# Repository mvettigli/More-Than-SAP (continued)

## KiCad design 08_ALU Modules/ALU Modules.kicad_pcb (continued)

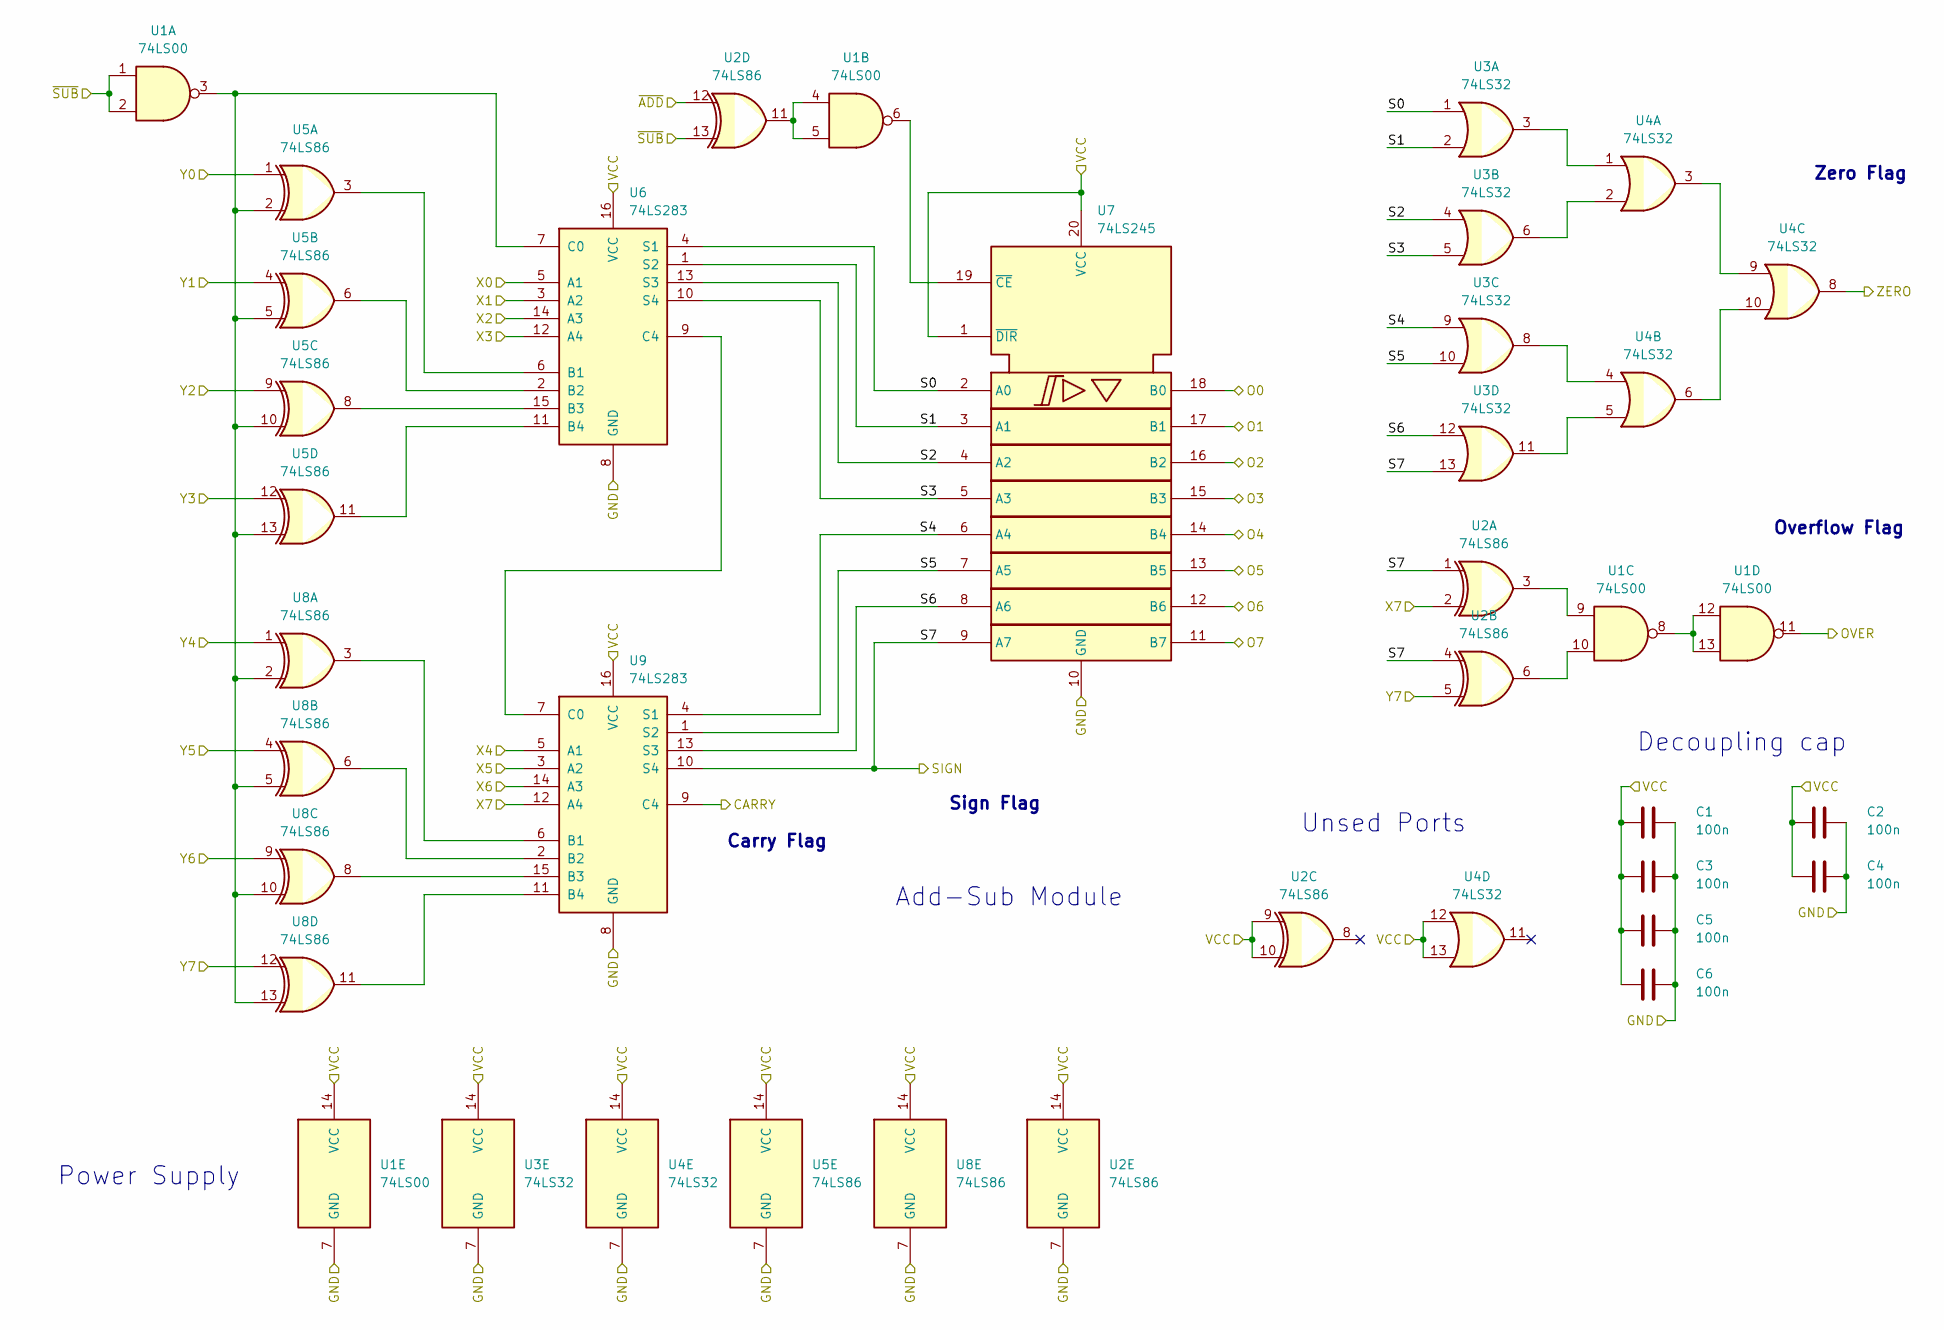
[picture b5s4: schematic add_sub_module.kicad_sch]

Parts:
C1, C2, C3, C4, C5, C6: 100n; C_Disc_D3.0mm_W1.6mm_P2.50mm
U1: 74LS00; DIP-14_W7.62mm
U2, U5, U8: 74LS86; DIP-14_W7.62mm
U3, U4: 74LS32; DIP-14_W7.62mm
U6, U9: 74LS283; DIP-16_W7.62mm
U7: 74LS245; DIP-20_W7.62mm

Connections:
/Add-Sub Module/S0: U3.1, U6.4 (S1), U7.2 (A0)
/Add-Sub Module/S1: U3.2, U6.1 (S2), U7.3 (A1)
/Add-Sub Module/S2: U3.4, U6.13 (S3), U7.4 (A2)
/Add-Sub Module/S3: U3.5, U6.10 (S4), U7.5 (A3)
/Add-Sub Module/S4: U3.9, U7.6 (A4), U9.4 (S1)
/Add-Sub Module/S5: U3.10, U7.7 (A5), U9.1 (S2)
/Add-Sub Module/S6: U3.12, U7.8 (A6), U9.13 (S3)
CARRY: U9.9 (C4); also elsewhere on the board
GND: C1.2, C2.2, C3.2, C4.2, C5.2, C6.2, U1.7 (GND), U2.7 (GND), U3.7 (GND), U4.7 (GND), U5.7 (GND), U6.8 (GND), U7.10 (GND), U8.7 (GND), U9.8 (GND); also elsewhere on the board
unnamed: U1.4, U1.5, U2.11
unnamed: U1.9, U2.3
unnamed: U1.10, U2.6
unnamed: U1.8, U1.12, U1.13
unnamed: U3.3, U4.1
unnamed: U3.6, U4.2
unnamed: U3.8, U4.4
unnamed: U3.11, U4.5
unnamed: U4.3, U4.9
unnamed: U4.6, U4.10
unnamed: U5.3, U6.6 (B1)
unnamed: U5.6, U6.2 (B2)
unnamed: U5.8, U6.15 (B3)
unnamed: U5.11, U6.11 (B4)
unnamed: U1.3, U5.2, U5.5, U5.10, U5.13, U6.7 (C0), U8.2, U8.5, U8.10, U8.13
unnamed: U6.9 (C4), U9.7 (C0)
unnamed: U1.6, U7.19 (~CE)
unnamed: U8.3, U9.6 (B1)
unnamed: U8.6, U9.2 (B2)
unnamed: U8.8, U9.15 (B3)
unnamed: U8.11, U9.11 (B4)
O0: U7.18 (B0); also elsewhere on the board
O1: U7.17 (B1); also elsewhere on the board
O2: U7.16 (B2); also elsewhere on the board
O3: U7.15 (B3); also elsewhere on the board
O4: U7.14 (B4); also elsewhere on the board
O5: U7.13 (B5); also elsewhere on the board
O6: U7.12 (B6); also elsewhere on the board
O7: U7.11 (B7); also elsewhere on the board
OVER: U1.11; also elsewhere on the board
SIGN: U2.1, U2.4, U3.13, U7.9 (A7), U9.10 (S4); also elsewhere on the board
VCC: C1.1, C2.1, C3.1, C4.1, C5.1, C6.1, U1.14 (VCC), U2.9, U2.10, U2.14 (VCC), U3.14 (VCC), U4.12, U4.13, U4.14 (VCC), U5.14 (VCC), U6.16 (VCC), U7.1 (~DIR), U7.20 (VCC), U8.14 (VCC), U9.16 (VCC); also elsewhere on the board
X0: U6.5 (A1); also elsewhere on the board
X1: U6.3 (A2); also elsewhere on the board
X2: U6.14 (A3); also elsewhere on the board
X3: U6.12 (A4); also elsewhere on the board
X4: U9.5 (A1); also elsewhere on the board
X5: U9.3 (A2); also elsewhere on the board
X6: U9.14 (A3); also elsewhere on the board
X7: U2.2, U9.12 (A4); also elsewhere on the board
Y0: U5.1; also elsewhere on the board
Y1: U5.4; also elsewhere on the board
Y2: U5.9; also elsewhere on the board
Y3: U5.12; also elsewhere on the board
Y4: U8.1; also elsewhere on the board
Y5: U8.4; also elsewhere on the board
Y6: U8.9; also elsewhere on the board
Y7: U2.5, U8.12; also elsewhere on the board
ZERO: U4.8; also elsewhere on the board
~ADD: U2.12; also elsewhere on the board
~SUB: U1.1, U1.2, U2.13; also elsewhere on the board

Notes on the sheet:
Carry Flag
Decoupling cap
Add-Sub Module
Unsed Ports
Sign Flag
Zero Flag
Power Supply
Overflow Flag

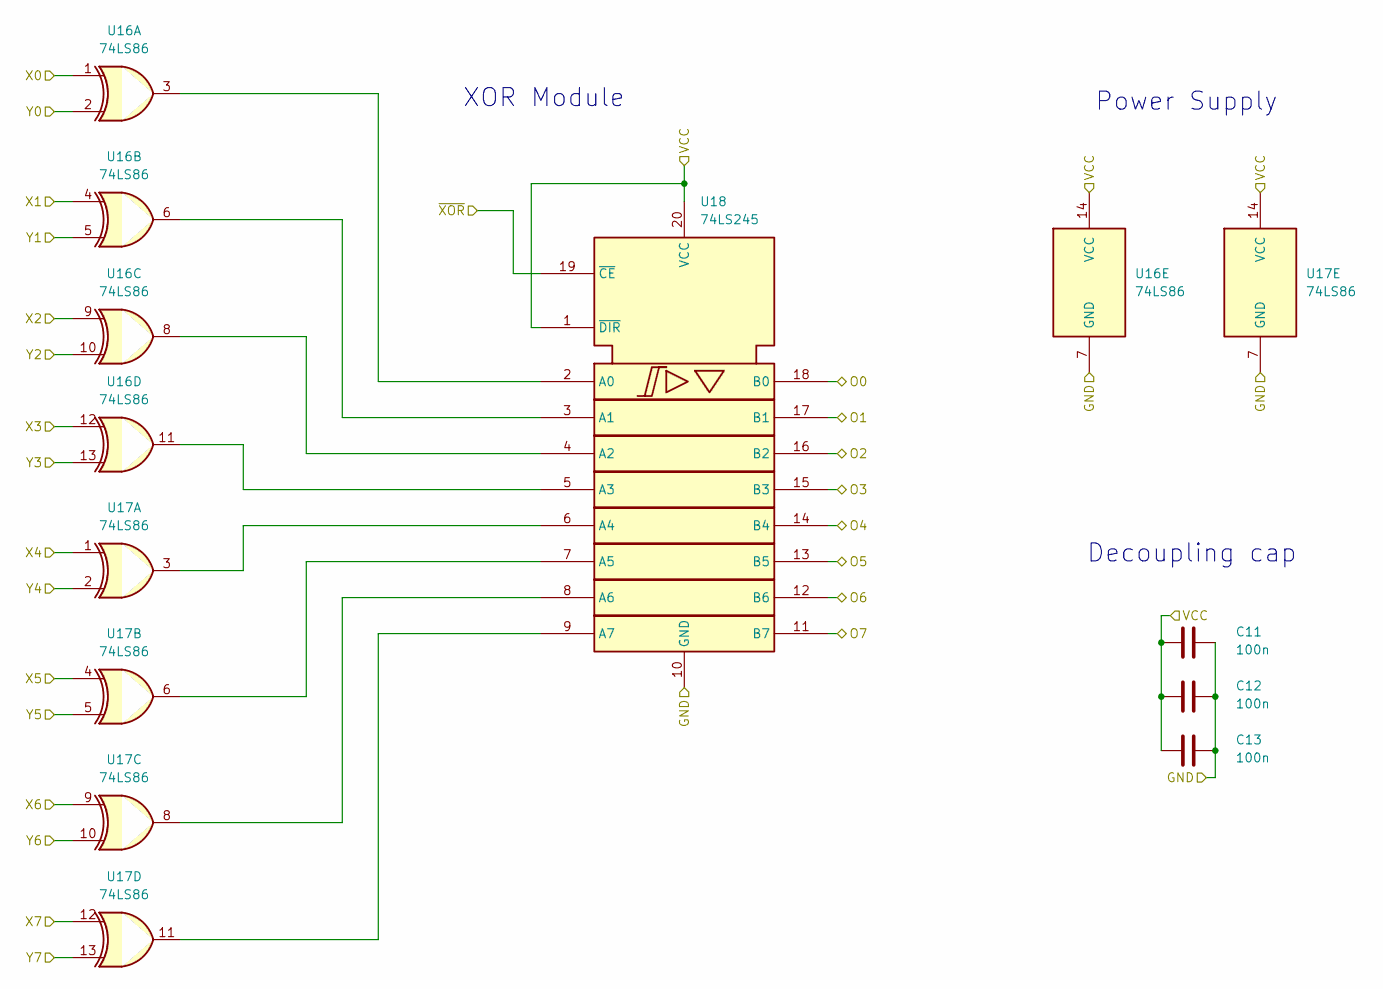
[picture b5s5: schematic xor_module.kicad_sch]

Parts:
C11, C12, C13: 100n; C_Disc_D3.0mm_W1.6mm_P2.50mm
U16, U17: 74LS86; DIP-14_W7.62mm
U18: 74LS245; DIP-20_W7.62mm

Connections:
GND: C11.2, C12.2, C13.2, U16.7 (GND), U17.7 (GND), U18.10 (GND); also elsewhere on the board
unnamed: U16.3, U18.2 (A0)
unnamed: U16.6, U18.3 (A1)
unnamed: U16.8, U18.4 (A2)
unnamed: U16.11, U18.5 (A3)
unnamed: U17.3, U18.6 (A4)
unnamed: U17.6, U18.7 (A5)
unnamed: U17.8, U18.8 (A6)
unnamed: U17.11, U18.9 (A7)
O0: U18.18 (B0); also elsewhere on the board
O1: U18.17 (B1); also elsewhere on the board
O2: U18.16 (B2); also elsewhere on the board
O3: U18.15 (B3); also elsewhere on the board
O4: U18.14 (B4); also elsewhere on the board
O5: U18.13 (B5); also elsewhere on the board
O6: U18.12 (B6); also elsewhere on the board
O7: U18.11 (B7); also elsewhere on the board
VCC: C11.1, C12.1, C13.1, U16.14 (VCC), U17.14 (VCC), U18.1 (~DIR), U18.20 (VCC); also elsewhere on the board
X0: U16.1; also elsewhere on the board
X1: U16.4; also elsewhere on the board
X2: U16.9; also elsewhere on the board
X3: U16.12; also elsewhere on the board
X4: U17.1; also elsewhere on the board
X5: U17.4; also elsewhere on the board
X6: U17.9; also elsewhere on the board
X7: U17.12; also elsewhere on the board
Y0: U16.2; also elsewhere on the board
Y1: U16.5; also elsewhere on the board
Y2: U16.10; also elsewhere on the board
Y3: U16.13; also elsewhere on the board
Y4: U17.2; also elsewhere on the board
Y5: U17.5; also elsewhere on the board
Y6: U17.10; also elsewhere on the board
Y7: U17.13; also elsewhere on the board
~XOR: U18.19 (~CE); also elsewhere on the board

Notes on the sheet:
Decoupling cap
Power Supply
XOR Module

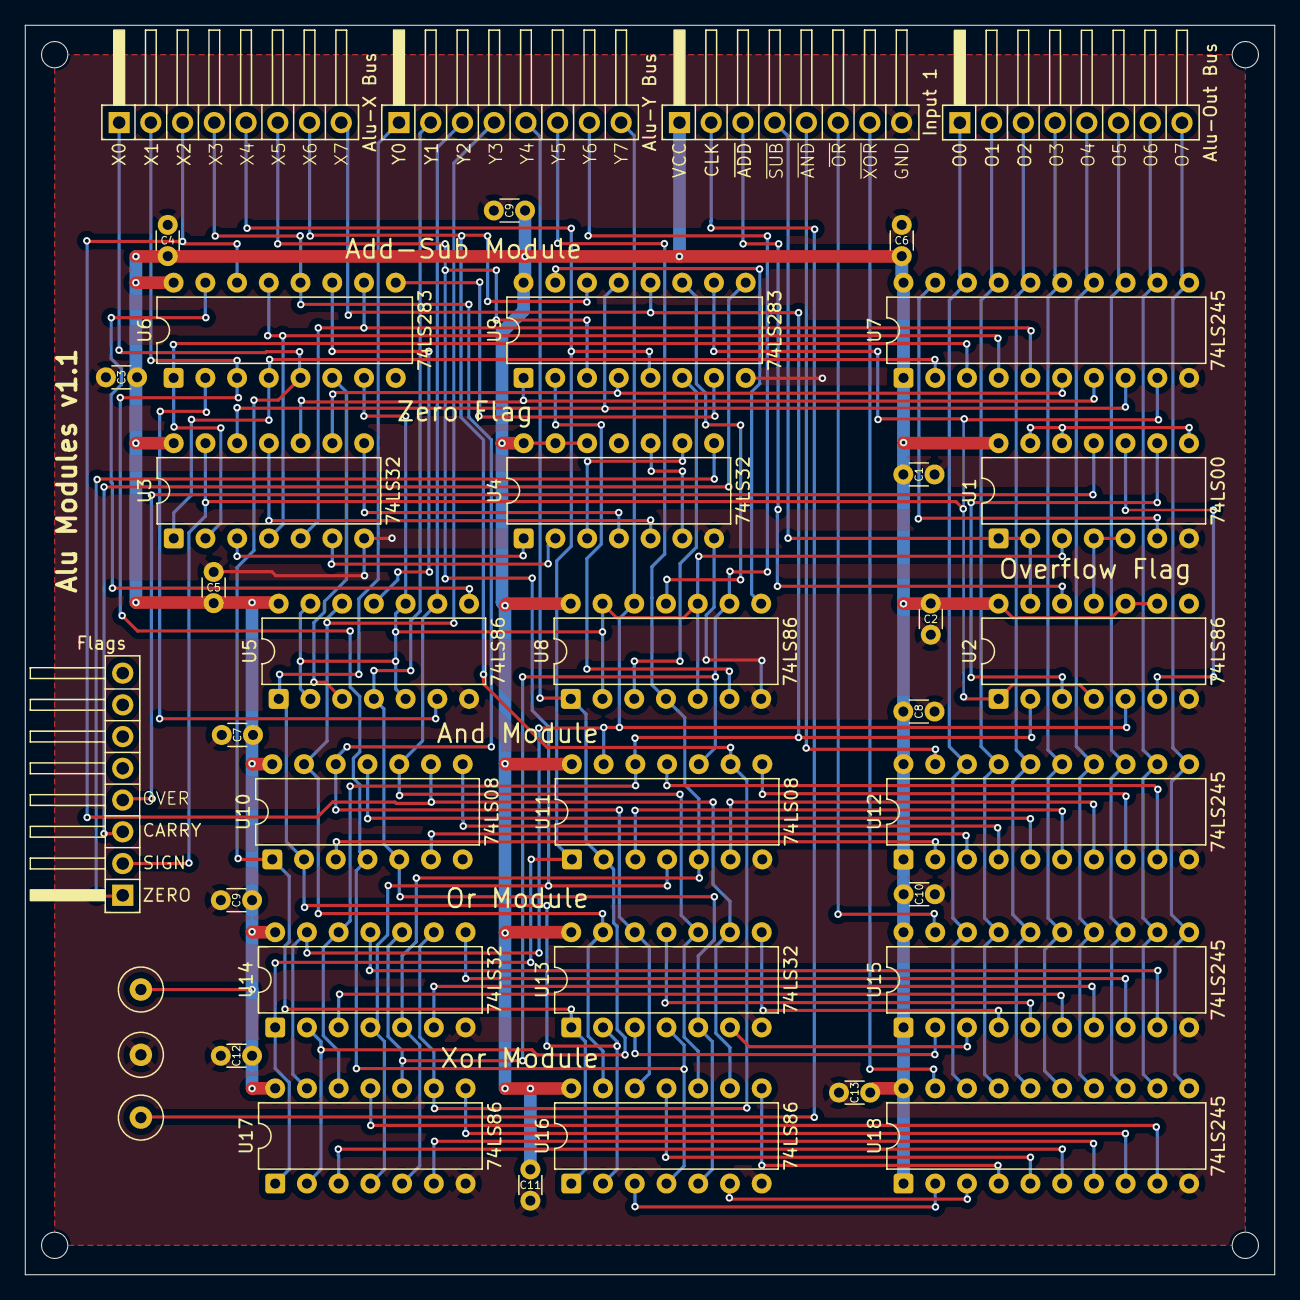
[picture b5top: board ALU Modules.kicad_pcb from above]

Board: 2 copper layers, 100.0 x 100.0 mm, 40 parts (0 on the bottom side), 88 nets.

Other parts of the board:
C9#2: 100n; C_Disc_D3.0mm_W1.6mm_P2.50mm

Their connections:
GND: C9#2.2; also elsewhere on the board
VCC: C9#2.1; also elsewhere on the board

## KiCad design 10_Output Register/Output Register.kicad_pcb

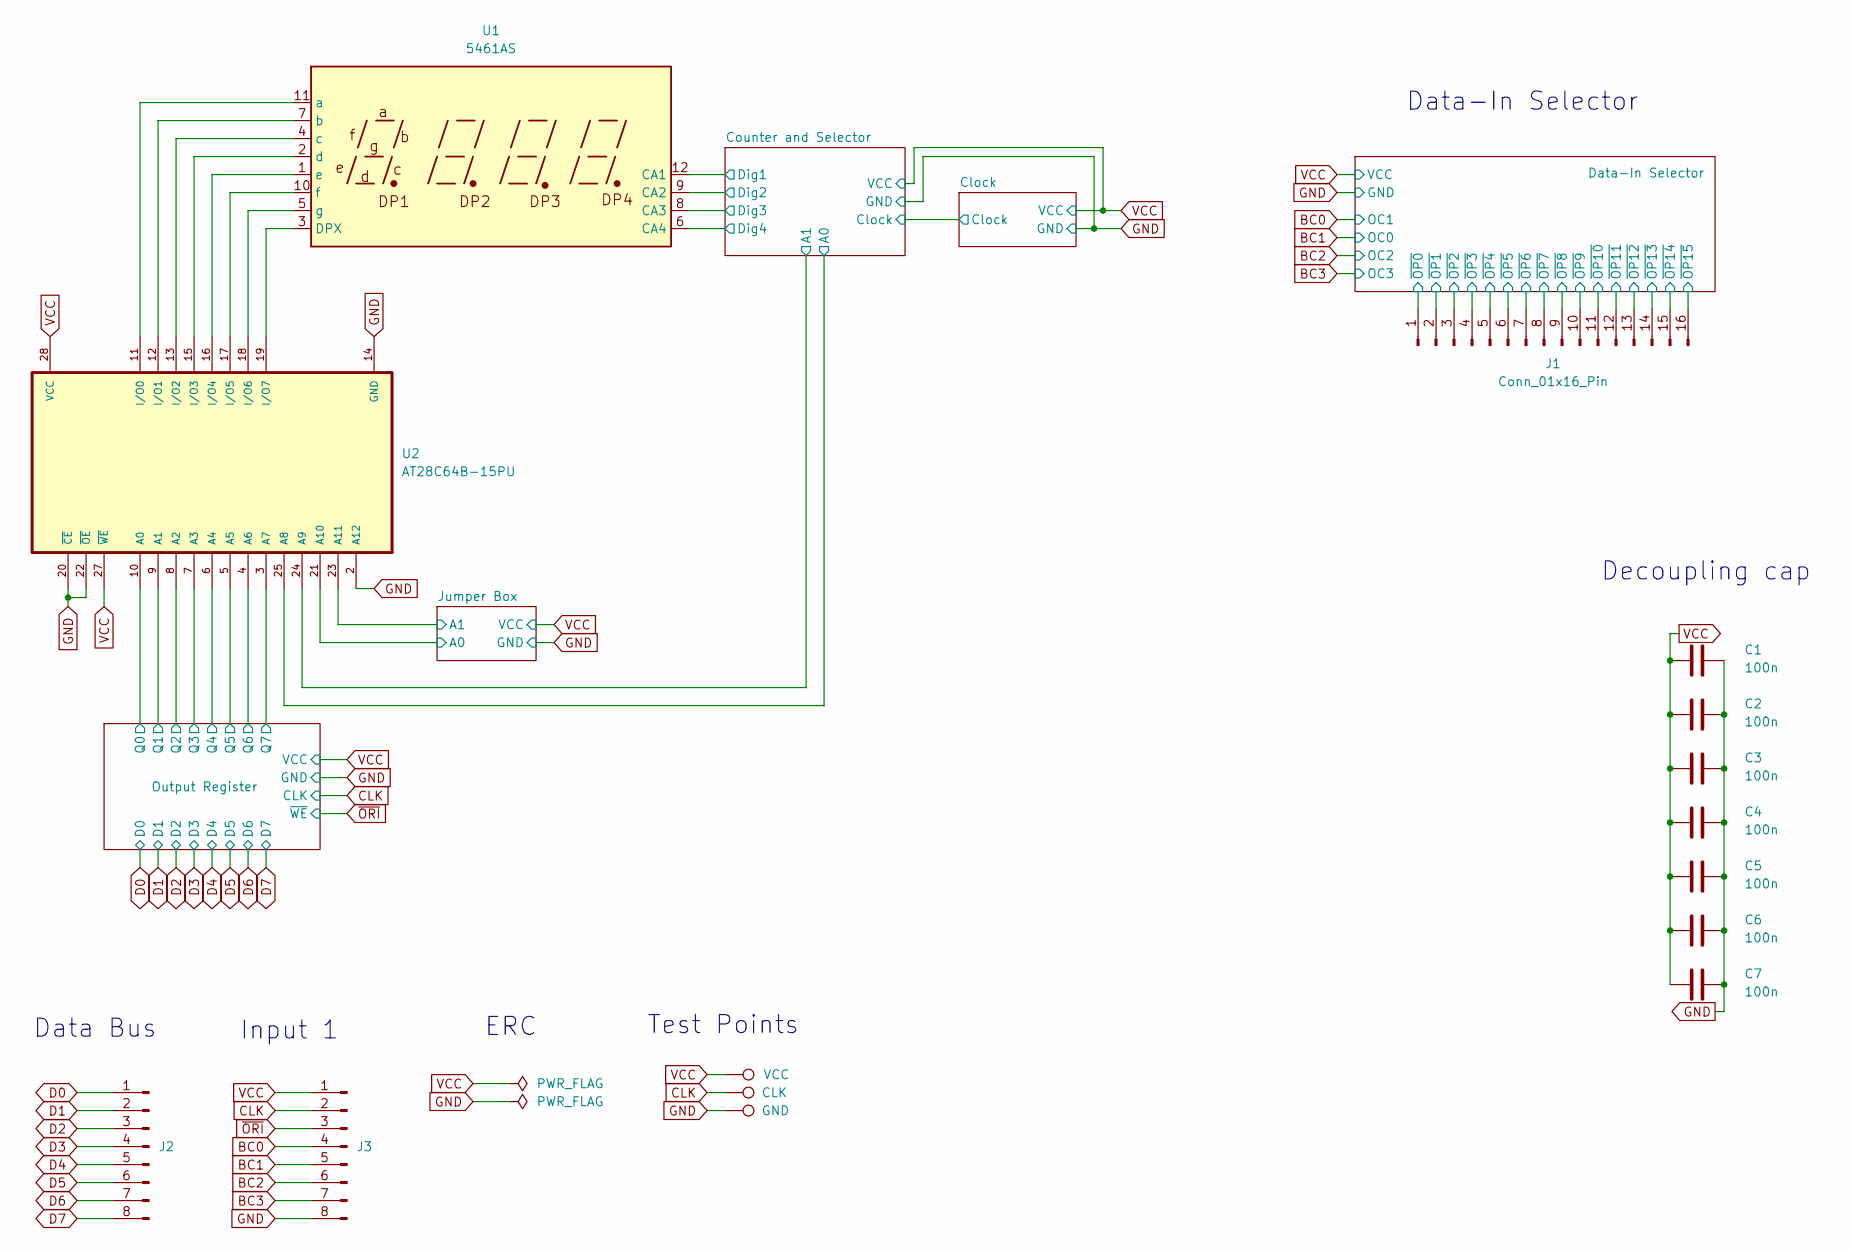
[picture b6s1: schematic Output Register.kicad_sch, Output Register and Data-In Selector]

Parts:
C1, C2, C3, C4, C5, C6, C7: 100n; C_Disc_D3.0mm_W1.6mm_P2.50mm
J1: Conn_01x16_Pin; PinHeader_2x08_P2.54mm_Horizontal
J2: Data bus; PinHeader_1x08_P2.54mm_Horizontal
J3: Input 1; PinHeader_1x08_P2.54mm_Horizontal
TP1: VCC; TestPoint_Loop_D3.50mm_Drill0.9mm_Beaded
TP2: CLK; TestPoint_Loop_D3.50mm_Drill0.9mm_Beaded
TP3: GND; TestPoint_Loop_D3.50mm_Drill0.9mm_Beaded
U1: 5461AS; CA56-12SURKWA
U2: AT28C64B-15PU; DIP1555W45P254L3733H482Q28; PARTREV B

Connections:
/Counter and Selector/A0: U2.25 (A8); also elsewhere on the board
/Counter and Selector/A1: U2.24 (A9); also elsewhere on the board
/Counter and Selector/Dig1: U1.12 (CA1); also elsewhere on the board
/Counter and Selector/Dig2: U1.9 (CA2); also elsewhere on the board
/Counter and Selector/Dig3: U1.8 (CA3); also elsewhere on the board
/Counter and Selector/Dig4: U1.6 (CA4); also elsewhere on the board
/Data-In Selector/~OP0: J1.1; also elsewhere on the board
/Data-In Selector/~OP1: J1.2; also elsewhere on the board
/Data-In Selector/~OP2: J1.3; also elsewhere on the board
/Data-In Selector/~OP3: J1.4; also elsewhere on the board
/Data-In Selector/~OP4: J1.5; also elsewhere on the board
/Data-In Selector/~OP5: J1.6; also elsewhere on the board
/Data-In Selector/~OP6: J1.7; also elsewhere on the board
/Data-In Selector/~OP7: J1.8; also elsewhere on the board
/Data-In Selector/~OP8: J1.9; also elsewhere on the board
/Data-In Selector/~OP9: J1.10; also elsewhere on the board
/Data-In Selector/~OP10: J1.11; also elsewhere on the board
/Data-In Selector/~OP11: J1.12; also elsewhere on the board
/Data-In Selector/~OP12: J1.13; also elsewhere on the board
/Data-In Selector/~OP13: J1.14; also elsewhere on the board
/Data-In Selector/~OP14: J1.15; also elsewhere on the board
/Data-In Selector/~OP15: J1.16; also elsewhere on the board
/Jumper Box/A0: U2.21 (A10); also elsewhere on the board
/Jumper Box/A1: U2.23 (A11); also elsewhere on the board
/Output Register/Q0: U2.10 (A0); also elsewhere on the board
/Output Register/Q1: U2.9 (A1); also elsewhere on the board
/Output Register/Q2: U2.8 (A2); also elsewhere on the board
/Output Register/Q3: U2.7 (A3); also elsewhere on the board
/Output Register/Q4: U2.6 (A4); also elsewhere on the board
/Output Register/Q5: U2.5 (A5); also elsewhere on the board
/Output Register/Q6: U2.4 (A6); also elsewhere on the board
/Output Register/Q7: U2.3 (A7); also elsewhere on the board
BC0: J3.4; also elsewhere on the board
BC1: J3.5; also elsewhere on the board
BC2: J3.6; also elsewhere on the board
BC3: J3.7; also elsewhere on the board
CLK: J3.2, TP2.1; also elsewhere on the board
D0: J2.1; also elsewhere on the board
D1: J2.2; also elsewhere on the board
D2: J2.3; also elsewhere on the board
D3: J2.4; also elsewhere on the board
D4: J2.5; also elsewhere on the board
D5: J2.6; also elsewhere on the board
D6: J2.7; also elsewhere on the board
D7: J2.8; also elsewhere on the board
GND: C1.2, C2.2, C3.2, C4.2, C5.2, C6.2, C7.2, J3.8, TP3.1, U2.2 (A12), U2.14 (GND), U2.20 (~CE), U2.22 (~OE); also elsewhere on the board
unnamed: U1.3 (DPX), U2.19 (I/O7)
unnamed: U1.11 (a), U2.11 (I/O0)
unnamed: U1.7 (b), U2.12 (I/O1)
unnamed: U1.4 (c), U2.13 (I/O2)
unnamed: U1.2 (d), U2.15 (I/O3)
unnamed: U1.1 (e), U2.16 (I/O4)
unnamed: U1.10 (f), U2.17 (I/O5)
unnamed: U1.5 (g), U2.18 (I/O6)
VCC: C1.1, C2.1, C3.1, C4.1, C5.1, C6.1, C7.1, J3.1, TP1.1, U2.27 (~WE), U2.28 (VCC); also elsewhere on the board
~ORI: J3.3; also elsewhere on the board

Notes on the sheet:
Decoupling cap
ERC
Test Points
Data Bus
Data-In Selector
Input 1

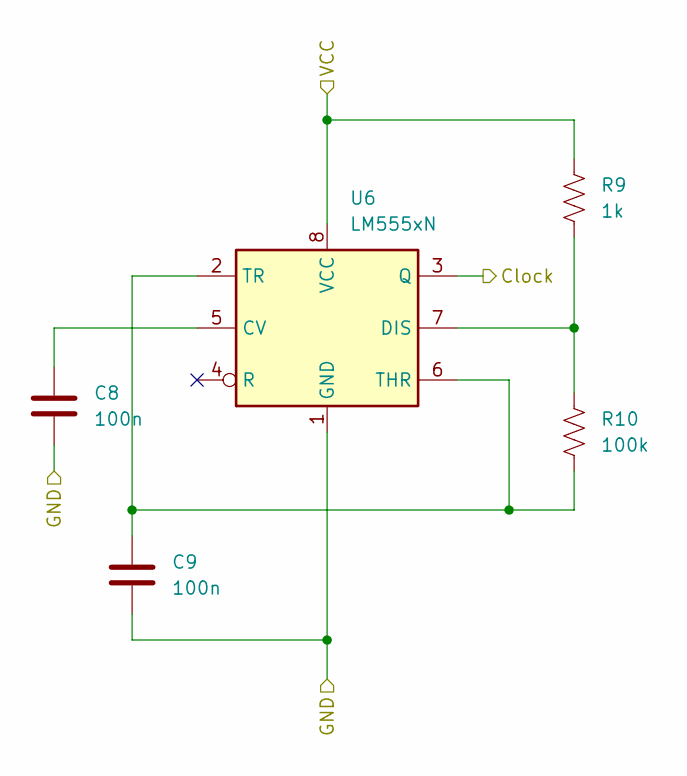
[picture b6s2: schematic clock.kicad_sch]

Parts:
C8, C9: 100n; C_Disc_D3.0mm_W1.6mm_P2.50mm
R9: 1k; R_Axial_DIN0207_L6.3mm_D2.5mm_P10.16mm_Horizontal
R10: 100k; R_Axial_DIN0207_L6.3mm_D2.5mm_P10.16mm_Horizontal
U6: LM555xN; DIP-8_W7.62mm

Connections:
/Clock/Clock: U6.3 (Q); also elsewhere on the board
GND: C8.2, C9.2, U6.1 (GND); also elsewhere on the board
unnamed: C8.1, U6.5 (CV)
unnamed: R9.2, R10.1, U6.7 (DIS)
unnamed: C9.1, R10.2, U6.2 (TR), U6.6 (THR)
VCC: R9.1, U6.8 (VCC); also elsewhere on the board

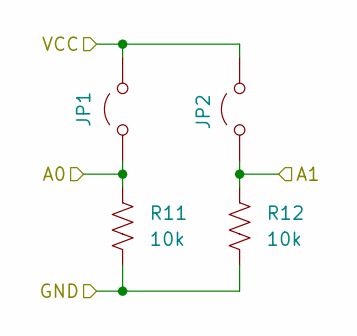
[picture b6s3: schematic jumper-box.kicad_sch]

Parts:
JP1, JP2: Jumper_2_Open; PinHeader_1x02_P2.54mm_Vertical
R11, R12: 10k; R_Axial_DIN0207_L6.3mm_D2.5mm_P10.16mm_Horizontal

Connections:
/Jumper Box/A0: JP1.1 (A), R11.1; also elsewhere on the board
/Jumper Box/A1: JP2.1 (A), R12.1; also elsewhere on the board
GND: R11.2, R12.2; also elsewhere on the board
VCC: JP1.2 (B), JP2.2 (B); also elsewhere on the board

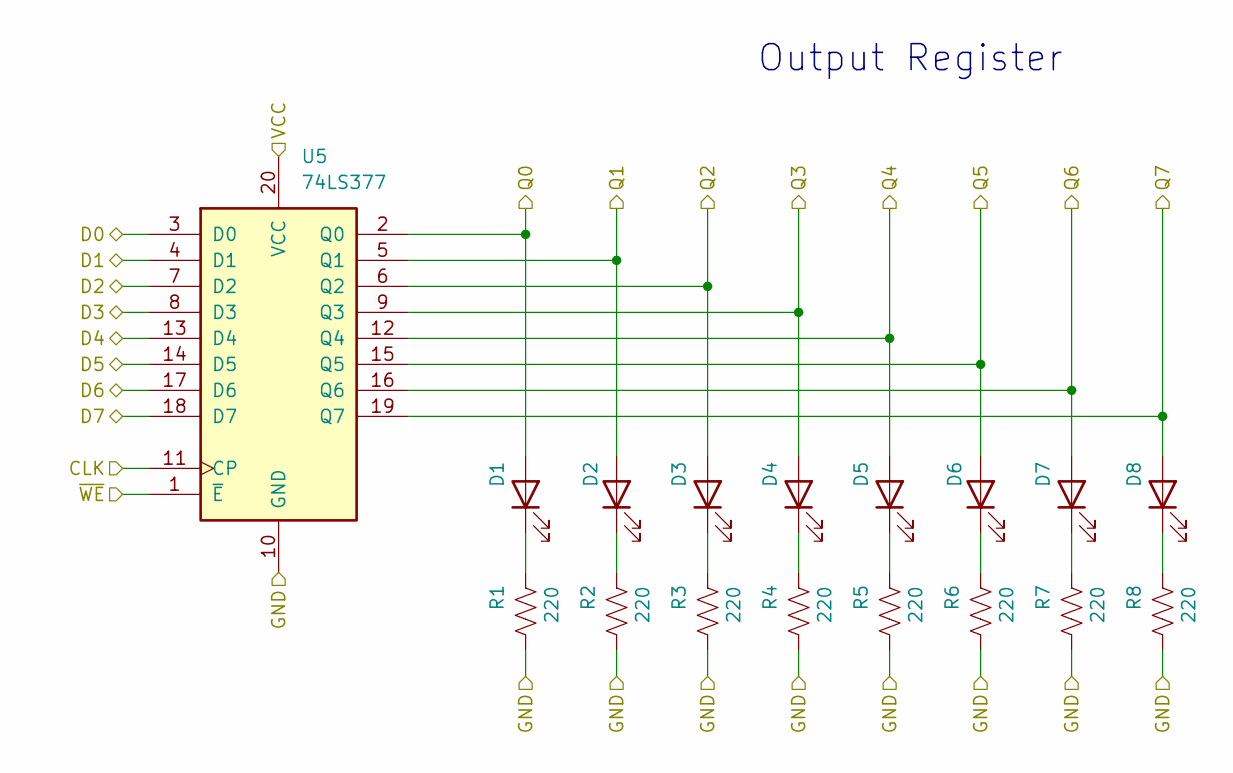
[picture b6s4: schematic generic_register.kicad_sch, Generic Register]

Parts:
D1, D2, D3, D4, D5, D6, D7, D8: RED; LED_D3.0mm
R1, R2, R3, R4, R5, R6, R7, R8: 220; R_Axial_DIN0207_L6.3mm_D2.5mm_P10.16mm_Horizontal
U5: 74LS377; DIP-20_W7.62mm

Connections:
/Output Register/Q0: D1.2 (A), U5.2 (Q0); also elsewhere on the board
/Output Register/Q1: D2.2 (A), U5.5 (Q1); also elsewhere on the board
/Output Register/Q2: D3.2 (A), U5.6 (Q2); also elsewhere on the board
/Output Register/Q3: D4.2 (A), U5.9 (Q3); also elsewhere on the board
/Output Register/Q4: D5.2 (A), U5.12 (Q4); also elsewhere on the board
/Output Register/Q5: D6.2 (A), U5.15 (Q5); also elsewhere on the board
/Output Register/Q6: D7.2 (A), U5.16 (Q6); also elsewhere on the board
/Output Register/Q7: D8.2 (A), U5.19 (Q7); also elsewhere on the board
CLK: U5.11 (CP); also elsewhere on the board
D0: U5.3 (D0); also elsewhere on the board
D1: U5.4 (D1); also elsewhere on the board
D2: U5.7 (D2); also elsewhere on the board
D3: U5.8 (D3); also elsewhere on the board
D4: U5.13 (D4); also elsewhere on the board
D5: U5.14 (D5); also elsewhere on the board
D6: U5.17 (D6); also elsewhere on the board
D7: U5.18 (D7); also elsewhere on the board
GND: R1.2, R2.2, R3.2, R4.2, R5.2, R6.2, R7.2, R8.2, U5.10 (GND); also elsewhere on the board
unnamed: D1.1 (K), R1.1
unnamed: D2.1 (K), R2.1
unnamed: D3.1 (K), R3.1
unnamed: D4.1 (K), R4.1
unnamed: D5.1 (K), R5.1
unnamed: D6.1 (K), R6.1
unnamed: D7.1 (K), R7.1
unnamed: D8.1 (K), R8.1
VCC: U5.20 (VCC); also elsewhere on the board
~ORI: U5.1 (~E); also elsewhere on the board

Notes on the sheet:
Output Register

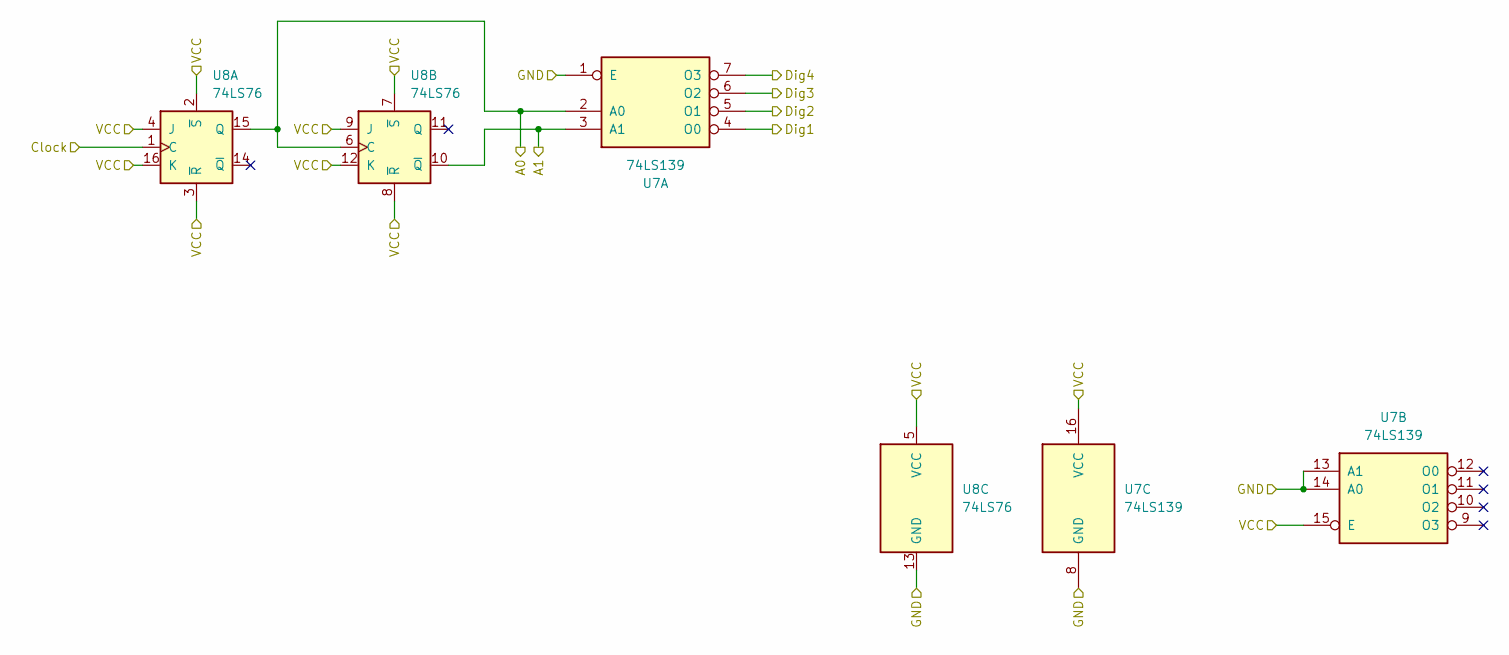
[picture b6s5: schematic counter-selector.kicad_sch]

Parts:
U7: 74LS139; DIP-16_W7.62mm
U8: 74LS76; DIP-16_W7.62mm

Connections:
/Clock/Clock: U8.1 (C); also elsewhere on the board
/Counter and Selector/A0: U7.2 (A0), U8.6 (C), U8.15 (Q); also elsewhere on the board
/Counter and Selector/A1: U7.3 (A1), U8.10 (~Q); also elsewhere on the board
/Counter and Selector/Dig1: U7.4 (O0); also elsewhere on the board
/Counter and Selector/Dig2: U7.5 (O1); also elsewhere on the board
/Counter and Selector/Dig3: U7.6 (O2); also elsewhere on the board
/Counter and Selector/Dig4: U7.7 (O3); also elsewhere on the board
GND: U7.1 (E), U7.8 (GND), U7.13 (A1), U7.14 (A0), U8.13 (GND); also elsewhere on the board
VCC: U7.15 (E), U7.16 (VCC), U8.2 (~S), U8.3 (~R), U8.4 (J), U8.5 (VCC), U8.7 (~S), U8.8 (~R), U8.9 (J), U8.12 (K), U8.16 (K); also elsewhere on the board

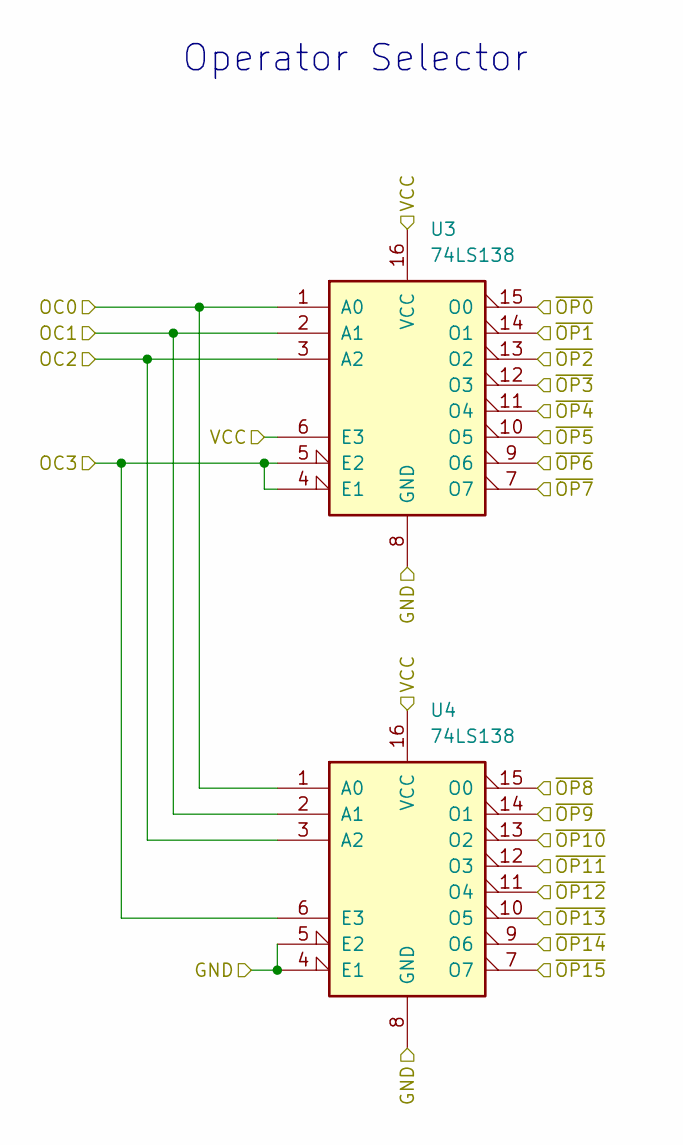
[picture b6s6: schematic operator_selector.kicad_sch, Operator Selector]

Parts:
U3, U4: 74LS138; DIP-16_W10.16mm

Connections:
/Data-In Selector/~OP0: U3.15 (O0); also elsewhere on the board
/Data-In Selector/~OP1: U3.14 (O1); also elsewhere on the board
/Data-In Selector/~OP2: U3.13 (O2); also elsewhere on the board
/Data-In Selector/~OP3: U3.12 (O3); also elsewhere on the board
/Data-In Selector/~OP4: U3.11 (O4); also elsewhere on the board
/Data-In Selector/~OP5: U3.10 (O5); also elsewhere on the board
/Data-In Selector/~OP6: U3.9 (O6); also elsewhere on the board
/Data-In Selector/~OP7: U3.7 (O7); also elsewhere on the board
/Data-In Selector/~OP8: U4.15 (O0); also elsewhere on the board
/Data-In Selector/~OP9: U4.14 (O1); also elsewhere on the board
/Data-In Selector/~OP10: U4.13 (O2); also elsewhere on the board
/Data-In Selector/~OP11: U4.12 (O3); also elsewhere on the board
/Data-In Selector/~OP12: U4.11 (O4); also elsewhere on the board
/Data-In Selector/~OP13: U4.10 (O5); also elsewhere on the board
/Data-In Selector/~OP14: U4.9 (O6); also elsewhere on the board
/Data-In Selector/~OP15: U4.7 (O7); also elsewhere on the board
BC0: U3.2 (A1), U4.2 (A1); also elsewhere on the board
BC1: U3.1 (A0), U4.1 (A0); also elsewhere on the board
BC2: U3.3 (A2), U4.3 (A2); also elsewhere on the board
BC3: U3.4 (E1), U3.5 (E2), U4.6 (E3); also elsewhere on the board
GND: U3.8 (GND), U4.4 (E1), U4.5 (E2), U4.8 (GND); also elsewhere on the board
VCC: U3.6 (E3), U3.16 (VCC), U4.16 (VCC); also elsewhere on the board

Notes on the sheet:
Operator Selector

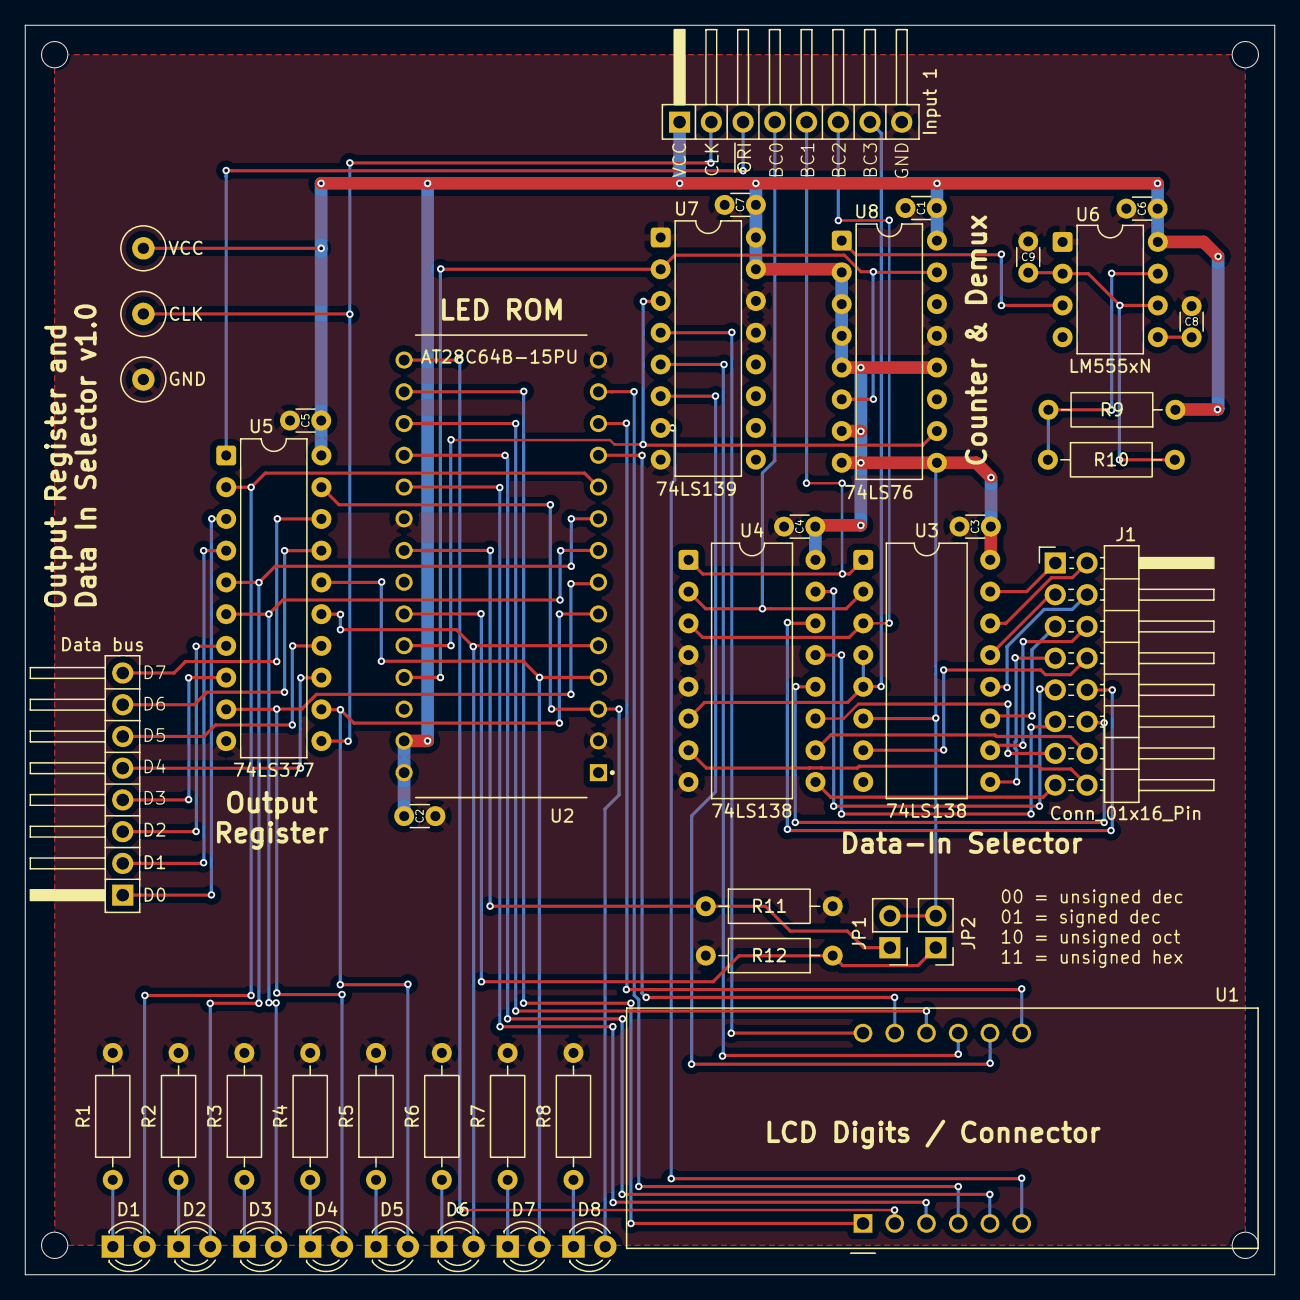
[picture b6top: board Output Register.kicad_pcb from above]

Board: 2 copper layers, 100.0 x 100.0 mm, 45 parts (0 on the bottom side), 68 nets.
